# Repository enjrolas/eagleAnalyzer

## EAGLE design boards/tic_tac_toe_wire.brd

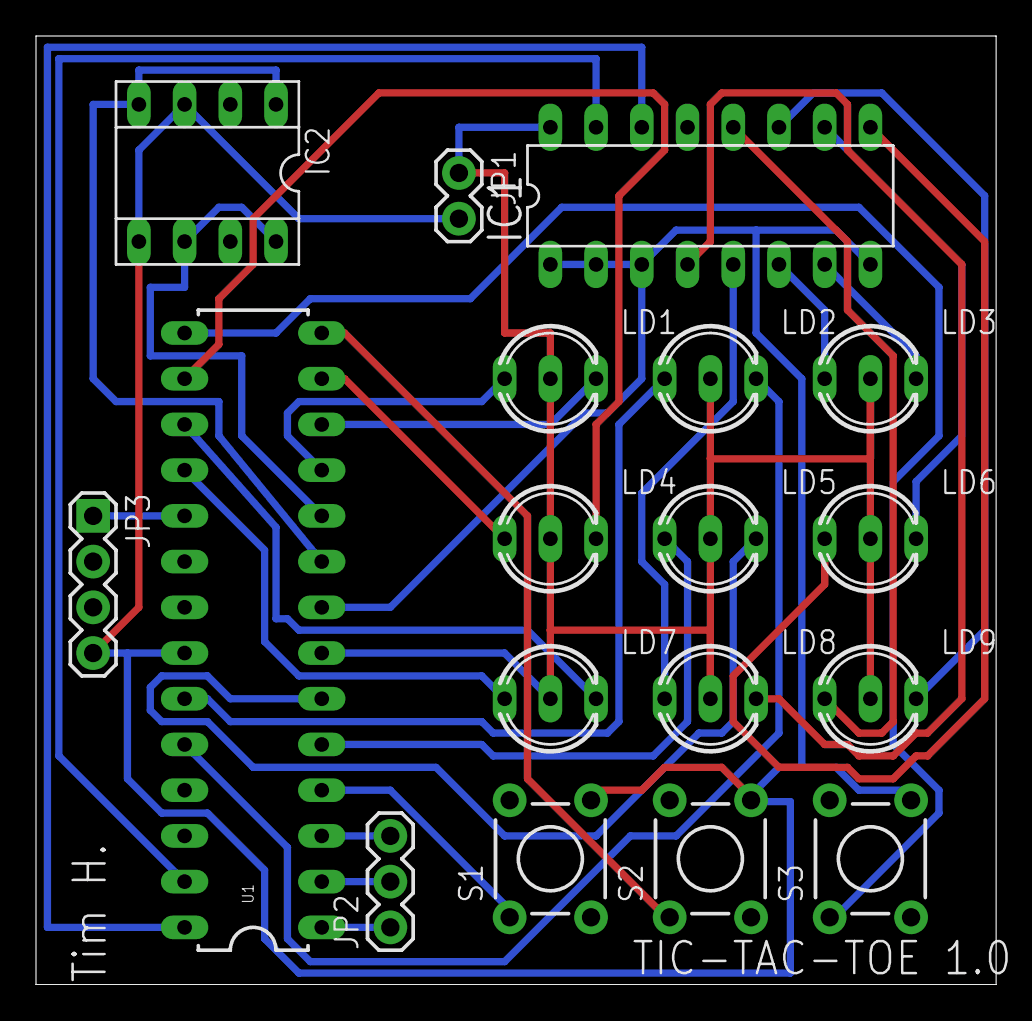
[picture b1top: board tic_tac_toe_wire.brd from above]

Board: 2 copper layers, 53.3 x 52.7 mm, 18 parts (0 on the bottom side), 31 nets.

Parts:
IC1: PCF8574P; DIL16
IC2: SOCKET-08
JP1: M02PTH; 1X02
JP2: 1X03
JP3: 1X04
LD1, LD2, LD3, LD4, LD5, LD6, LD7, LD8, LD9: DUOLED-C-5MM
S1, S2, S3: TACTILE-PTH
U1: ATMEGA328P_PDIP; DIL28-3

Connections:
GND: IC1.1, IC1.2, IC1.3, IC1.8, IC2.3, IC2.5, JP1.2, JP3.4, S1.4, S2.4, S3.4, U1.8, U1.22
unnamed: S1.1, U1.4
unnamed: S2.1, U1.14
unnamed: S3.1, U1.15
unnamed: IC1.14, U1.28
unnamed: IC1.15, U1.27
unnamed: JP2.2, U1.2
unnamed: JP2.1, U1.1
unnamed: JP2.3, U1.3
unnamed: JP3.1, U1.19
unnamed: IC2.6, IC2.8, U1.10
unnamed: IC2.1, IC2.4, U1.9
unnamed: IC1.12, LD9.AX
unnamed: IC1.11, LD9.AR
unnamed: IC1.10, LD6.AR
unnamed: IC1.9, LD6.AX
unnamed: IC1.7, LD3.AR
unnamed: IC1.6, LD3.AX
unnamed: IC1.5, LD8.AX
unnamed: IC1.4, LD8.AR
unnamed: LD7.AX, U1.18
unnamed: LD7.AR, U1.17
unnamed: LD4.AR, U1.16
unnamed: LD4.AX, U1.13
unnamed: LD1.AR, U1.12
unnamed: LD1.AX, U1.11
unnamed: LD5.AR, U1.6
unnamed: LD5.AX, U1.5
unnamed: LD2.AX, U1.23
unnamed: LD2.AR, U1.24
VCC: IC1.16, JP1.1, LD1.C, LD2.C, LD3.C, LD4.C, LD5.C, LD6.C, LD7.C, LD8.C, LD9.C, U1.7

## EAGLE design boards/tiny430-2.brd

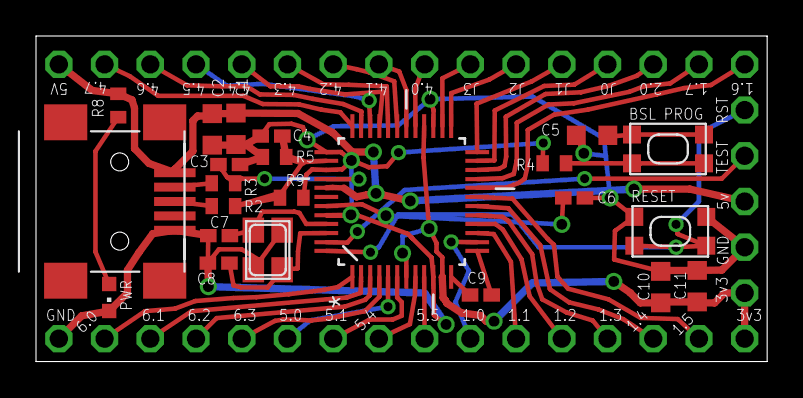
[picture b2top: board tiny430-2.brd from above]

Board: 2 copper layers, 40.6 x 18.1 mm, 60 parts (0 on the bottom side), 46 nets.

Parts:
C1, C5, C10, C11: 100nF; C0603K
C2: 10uF; C0603K
C3, C4: 10pF; C0402K
C6: 220nF; C0402K
C7, C8: 22pF; C0402K
C9: 470nF; C0402K
CN1: USB-MINIB
JP1, JP3, JP4, JP5, JP6, JP7, JP8, JP9, JP10, JP11, JP12, JP13, JP14, JP15, JP16, JP17, JP18, JP19, JP20, JP21, JP22, JP23, JP24, JP25, JP26, JP27, JP28, JP29, JP30, JP31, JP32, JP33, JP34, JP35, JP36, JP37: M01SMDNS; 1X01NS
JP2: GND; 1X01NS
PWR: CHIPLED_0603
Q1: NX3225
R2, R3: 27R; R0402
R4: 100R; R0402
R5: 1M/1%; R0402
R8: 330; R0402
R9: 1.5k; R0402
SW1: BSL; KMR2
SW2: RESET; KMR2
U1: MSP430F5510IPT; QFP50P900X900X160-48N

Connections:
1.0: JP9.1, U1.14
1.1: JP10.1, U1.15
1.2: JP11.1, U1.16
1.3: JP12.1, U1.17
1.4: JP13.1, U1.18
1.5: JP14.1, U1.19
1.6: JP37.1, U1.20
1.7: JP36.1, U1.21
2.0: JP35.1, U1.22
4.0: JP30.1, U1.29
4.1: JP29.1, U1.30
4.2: JP28.1, U1.31
4.3: JP27.1, U1.32
4.4: JP26.1, U1.33
4.5: JP25.1, U1.34
4.6: JP24.1, U1.35
4.7: JP23.1, U1.36
5.0: JP7.1, U1.5
5.1: JP8.1, U1.6
5.4: JP15.1, U1.8
5.5: JP16.1, U1.9
6.0: JP3.1, U1.1
6.1: JP4.1, U1.2
6.2: JP5.1, U1.3
6.3: JP6.1, U1.4
+3V3: C10.1, C11.1, JP17.1, JP22.1, U1.7, U1.11, U1.28
+5V: C1.2, C2.2, CN1.VBUS, JP1.1, JP20.1, R8.1, U1.41
GND: C1.1, C2.1, C3.2, C4.2, C5.2, C6.1, C7.2, C8.2, C9.1, C10.2, C11.2, CN1.GND, JP2.1, JP21.1, PWR.C, Q1.2, Q1.4, R5.1, SW2.1, SW2.3, U1.10, U1.12, U1.27, U1.37, U1.44
J0: JP34.1, U1.23
J1: JP33.1, U1.24
J2: JP32.1, U1.25
J3: JP31.1, U1.26
unnamed: CN1.D+, R2.2
unnamed: CN1.D-, R3.2
unnamed: C6.2, U1.43
unnamed: PWR.A, R8.2
unnamed: R4.1, R9.2, U1.39
unnamed: C5.1, SW1.2, SW1.4, U1.42
unnamed: R4.2, SW1.1, SW1.3
unnamed: C9.2, U1.13
unnamed: C3.1, R3.1, U1.40
unnamed: C4.1, R2.1, R5.2, R9.1, U1.38
unnamed: C7.1, Q1.3, U1.45
unnamed: C8.1, Q1.1, U1.46
RST: JP18.1, SW2.2, SW2.4, U1.48
TEST: JP19.1, U1.47

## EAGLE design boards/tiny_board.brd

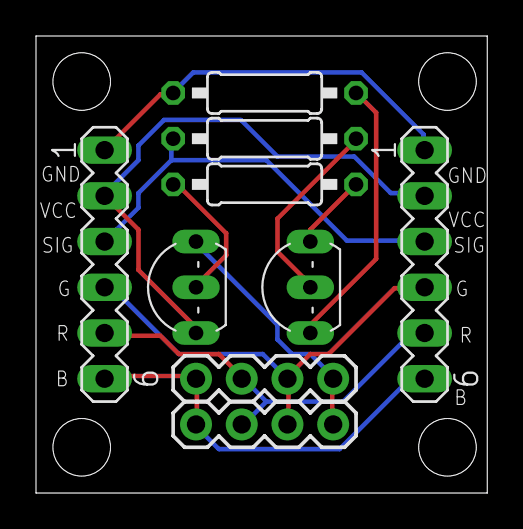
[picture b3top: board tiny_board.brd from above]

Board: 2 copper layers, 25.1 x 25.4 mm, 9 parts (0 on the bottom side), 11 nets.

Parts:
1, 2: MA06-1
Q1: 2N2907; TO92-EBC-OVAL
R1, R4: 100; 0207/10
R2: 360; 0207/10
STRIP, STRIP1: 1X4-BIG; 1X04-BIG
T1: 2N2222; TO92-EBC-OVAL

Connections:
BLUESIG: 1.6, 2.6, STRIP.4, STRIP1.4
GND: 1.1, 2.1, R2.2
GREENSIG: 1.5, 2.5, STRIP.3, STRIP1.3
unnamed: 1.3, 2.3, R1.1
unnamed: R2.1, T1.E
unnamed: Q1.B, R4.2
unnamed: R4.1, T1.C
unnamed: Q1.C, STRIP.1, STRIP1.1
unnamed: R1.2, T1.B
REDSIG: 1.4, 2.4, STRIP.2, STRIP1.2
VCC: 1.2, 2.2, Q1.E

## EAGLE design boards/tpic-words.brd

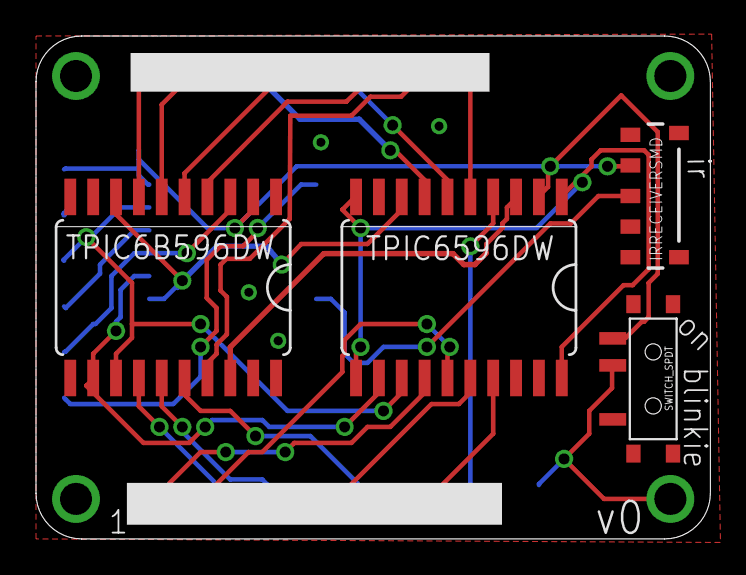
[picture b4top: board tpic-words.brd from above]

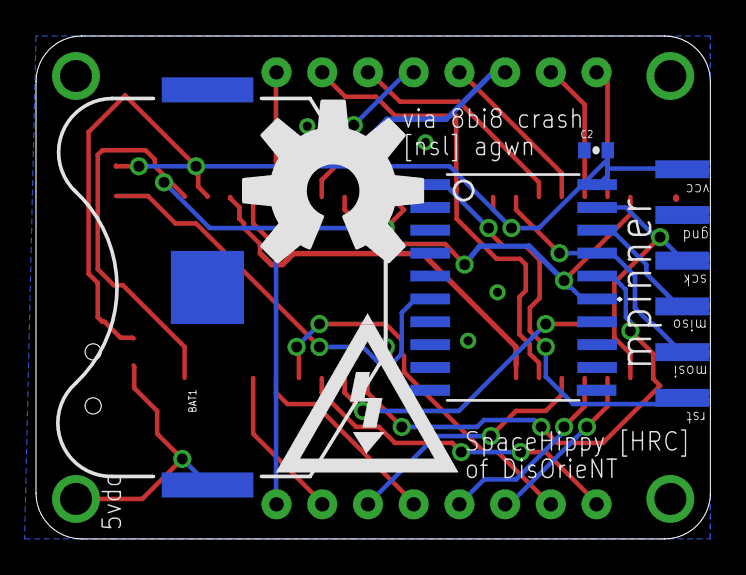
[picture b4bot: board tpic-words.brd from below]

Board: 2 copper layers, 37.5 x 27.9 mm, 13 parts (4 on the bottom side), 28 nets.

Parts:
BAT1: NSL_BATTICON_20MM_CLIPPED
C2: 0.1uF; 0402-CAP
H1, H2, H3, H4: SEW_HOLE-SMALL; SIMPLE_HOLE_SM
IC1: TPIC6B596DW; SO20W
IC2: TPIC6596DW; SO20W
LED1: SEGMENT-HEADERS
U$1: AVR-6_TINY2313-*S*; AVR-6_SO20L$
U$2: SWITCH_SPDT; KPS-1290
U$3: IRRECEIVERSMD; TSOP8523
U$4: 1X06_PIN_HEADER; 1X06_EDGE

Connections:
GND: BAT1.2, C2.1, H1.P$1, H3.P$1, H4.P$1, IC1.9, IC1.10, IC1.11, IC1.19, IC2.9, IC2.19, U$1.10, U$3.4, U$3.5, U$4.5
MISO: U$1.18, U$4.3
MOSI: IC1.3, U$1.17, U$4.2
unnamed: BAT1.1, H2.P$1, U$2.P
unnamed: IC1.7, LED1.16
unnamed: IC1.6, LED1.15
unnamed: IC1.5, LED1.13
unnamed: IC1.4, LED1.11
unnamed: IC1.17, LED1.10
unnamed: IC1.16, LED1.6
unnamed: IC1.15, LED1.4
unnamed: IC1.14, LED1.3
unnamed: IC1.18, IC2.3
unnamed: U$1.6, U$3.3
unnamed: IC1.12, IC2.12, U$1.16
unnamed: IC1.8, IC2.8, U$1.15
PGND: IC2.1, IC2.10, IC2.11, IC2.20
R-PIN1: IC2.14, LED1.1
R-PIN2: IC2.15, LED1.2
R-PIN3: IC2.16, LED1.5
R-PIN4: IC2.17, LED1.7
R-PIN5: IC2.4, LED1.8
R-PIN6: IC2.5, LED1.9
R-PIN7: IC2.6, LED1.12
R-PIN8: IC2.7, LED1.14
RESET: U$1.1, U$4.1
SCK: IC1.13, IC2.13, U$1.19, U$4.4
VCC: C2.2, IC1.2, IC2.2, U$1.20, U$2.S, U$3.2, U$4.6

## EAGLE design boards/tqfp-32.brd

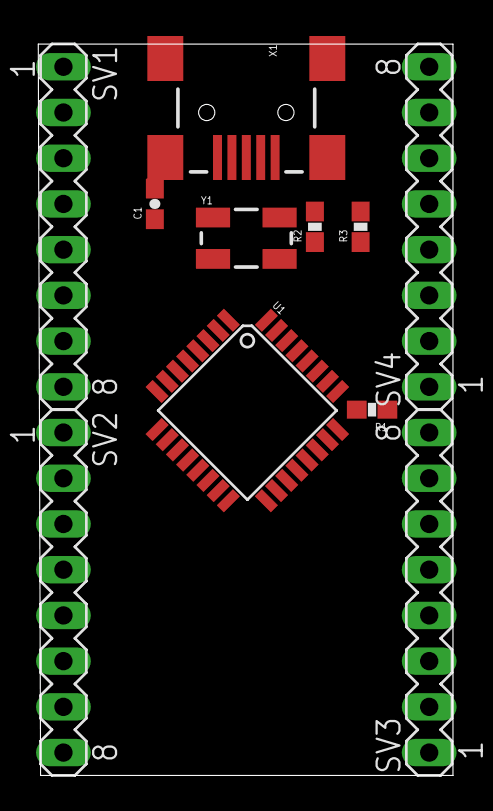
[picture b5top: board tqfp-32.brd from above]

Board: 2 copper layers, 23.0 x 40.6 mm, 11 parts (0 on the bottom side), 34 nets, no tracks yet.

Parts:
C1: 0.1uF; 0603-CAP
R1: 0603-RES
R2, R3: 68; 0603-RES
SV1: 1-8; MA08-1
SV2: 9-16; MA08-1
SV3: 17-24; MA08-1
SV4: 25-32; MA08-1
U1: ATMEGA8U2AU; TQFP32-08
X1: USBSMD; USB-MINIB
Y1: CRYSTAL-SMD-5X3

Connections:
1: U1.1, Y1.3
2: U1.2, Y1.1
3: SV1.3, U1.3
3V3: R1.2, SV1.4
5: SV1.5, U1.5
5V: C1.1, SV1.1, U1.4, U1.31, U1.32, X1.VBUS
6: SV1.6, U1.6
7: SV1.7, U1.7
8: SV1.8, U1.8
9: SV2.1, U1.9
10: SV2.2, U1.10
11: SV2.3, U1.11
12: SV2.4, U1.12
13: SV2.5, U1.13
14: SV2.6, U1.14
18: SV3.2, U1.18
19: SV3.3, U1.19
20: SV3.4, U1.20
21: SV3.5, U1.21
22: SV3.6, U1.22
23: SV3.7, U1.23
25: SV4.1, U1.25
26: SV4.2, U1.26
27: SV4.3, U1.27
28: SV4.4, U1.28
29: R2.1, SV4.5, U1.29
30: R3.1, SV4.6, U1.30
BUS_D+: R2.2, X1.D+
BUS_D-: R3.2, X1.D-
GND: C1.2, X1.GND
MISO: SV3.1, U1.17
MOSI: SV2.8, U1.16
RST: R1.1, SV3.8, U1.24
SCK: SV2.7, U1.15

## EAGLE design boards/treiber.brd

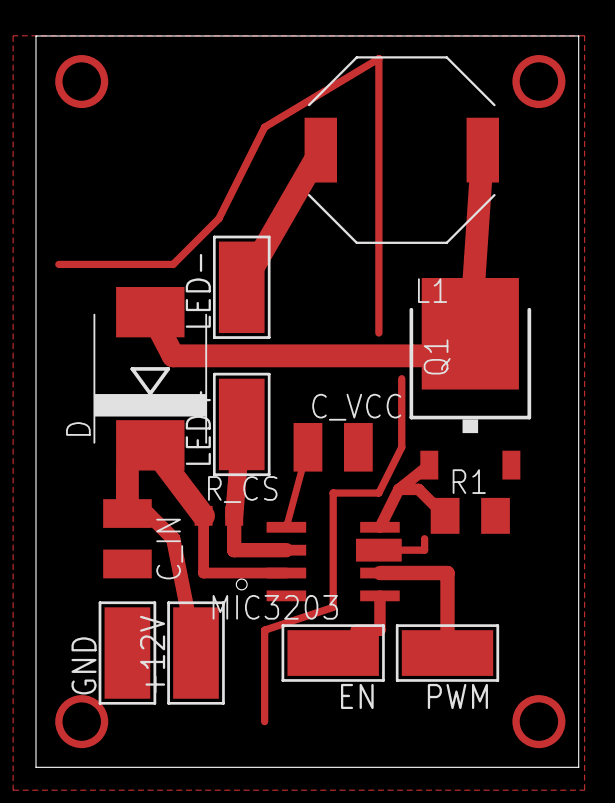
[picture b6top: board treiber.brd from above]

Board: 2 copper layers, 30.1 x 40.6 mm, 14 parts (0 on the bottom side), 9 nets.

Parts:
+12V: 5-2,5
C_IN: 10uf; C1210
C_VCC: 10F; C1210
D: 60V; SMC
EN: 5-2,5
GND: 5-2,5
L1: 47uH; WE-TPC_1028/1038
LED+: 5-2,5
LED-: 5-2,5
MIC3203: MIC3203; SO08
PWM: 5-2,5
Q1: IPD640N06L G; TO252
R1: 10k; M1206
R_CS: 0,16; R0603

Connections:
GND: C_IN.2, C_VCC.2, GND.1, MIC3203.4, MIC3203.7, Q1.2, R1.2
IRFU: MIC3203.8, Q1.1, R1.1
unnamed: L1.1, LED-.1
unnamed: +12V.1, C_IN.1, D.C, MIC3203.3, R_CS.1
unnamed: D.A, L1.2, Q1.3
unnamed: LED+.1, MIC3203.2, R_CS.2
unnamed: C_VCC.1, MIC3203.1
unnamed: EN.1, MIC3203.5
PWM: MIC3203.6, PWM.1

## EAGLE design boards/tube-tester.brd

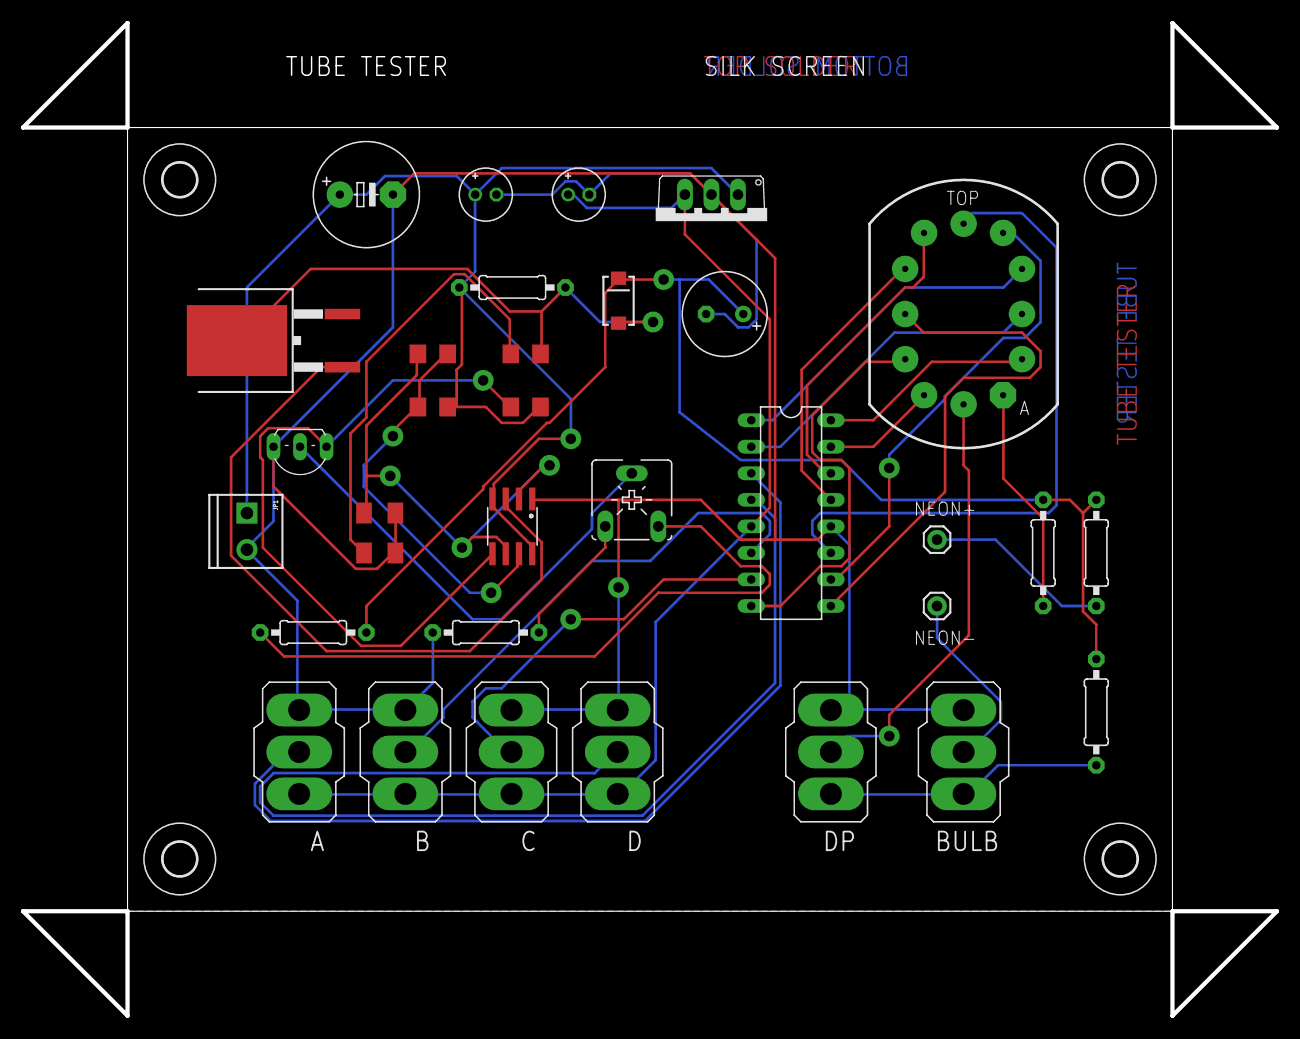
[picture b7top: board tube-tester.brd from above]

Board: 2 copper layers, 120.0 x 95.0 mm, 37 parts (0 on the bottom side), 32 nets.

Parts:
A: 320-916
B: 320-916
BULB: 320-916
C: 320-916
C1: 330uF; E5-10,5
C2: 2n2; C1206K
C3: 100pF; C1206K
C4: 2.2uF; E3,5-8
C5: 100uF; E2-5
C6: 10uF; E2-5
D: 320-916
D1: 1N4007; SMA-DIODE
DP: 320-916
IC1: NE555D; SO08
IC2: 74141N; DIL16
IC3: 7805; TO220V
JP1: SCREWTERMINAL-3.5MM-2
L1: 100uH; 0207/10
N1: IN-12BIN-12; IN-12
NEON+: M01PTH; 1X01
NEON-: M01PTH; 1X01
Q1: IRF740S; TO263
Q2: BC546; TO92-EBC
R1: 56K; R1206
R2: 10K; R1206
R3: 1K; R1206
R4: 470R; 0207/10
R5: 220K; 0207/10
R6: 2K2; R1206
R7, R8, R9: 22K; 0207/10
U$1, U$2, U$3, U$4: 3,2
VR1: 1K; CA6V

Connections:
GND: A.3, B.3, BULB.3, C.3, C1.-, C2.2, C3.2, C4.-, C5.-, C6.-, D.3, DP.3, IC1.1, IC2.12, IC3.2, JP1.2, Q2.E, R4.1
unnamed: IC1.3, Q1.1
unnamed: C3.1, R6.1
unnamed: IC1.5, Q2.C, R1.1
unnamed: IC1.7, R2.2, R3.1
unnamed: C2.1, IC1.2, IC1.6, R2.1
unnamed: D1.A, L1.1, Q1.3, R6.2
unnamed: C4.+, D1.C, R5.2, R7.2, R8.2, R9.2
unnamed: R5.1, VR1.E
unnamed: R4.2, VR1.A
unnamed: Q2.B, VR1.S
unnamed: IC2.15, N1.1
unnamed: IC2.8, N1.2
unnamed: IC2.9, N1.3
unnamed: IC2.13, N1.4
unnamed: IC2.14, N1.5
unnamed: IC2.11, N1.6
unnamed: IC2.10, N1.7
unnamed: IC2.1, N1.8
unnamed: IC2.2, N1.9
unnamed: IC2.16, N1.0
unnamed: N1.A, R7.1
unnamed: A.2, IC2.3
unnamed: B.2, IC2.6
unnamed: C.2, IC2.7
unnamed: D.2, IC2.4
unnamed: C1.+, C5.+, IC1.4, IC1.8, IC3.1, JP1.1, L1.2, R1.2, R3.2
unnamed: NEON+.1, R8.1
unnamed: BULB.2, NEON-.1
unnamed: A.1, B.1, C.1, C6.+, D.1, IC2.5, IC3.3
unnamed: DP.2, N1.LHDP
unnamed: BULB.1, DP.1, R9.1

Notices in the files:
parts and their libraries:
SparkFun-DigitalIC: Licensing: CC v3.0 Share-Alike You are welcome to use this library for commercial purposes.
